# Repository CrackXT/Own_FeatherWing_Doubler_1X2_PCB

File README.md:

# Own_FeatherWing_Doubler_1X2_PCB

PCB files for two Adafruit Feather/FeatherWing on one PCB (side by side)

# Description

Two Feather/FeatherWing can be placed side by side on this board.

The Doubler 1X2, has a tripple duplicate breakout for each pin on a Feather, as well as a bunch of plain grid development holes. Also, the three sets of pins are cross connected and for GND(- or black) and 3.3V(+ or red), they give you a full strip of connected pads.

The board can be produced here (AISLER) with the files (.brd and .sch) or by any other PCB manufacturer. -> https://aisler.net/

# Serie

- .dev

# Layout

Top<br>

Bottom<br>

Routing/Dimensions(inch)<br>

Schematic<br>
Schematic as .pdf at the top of the page.

# License

The design and layout is based on open source publications from Adafruit and has been modified for side-by-side assembly.

# Thanks!

Great work and many thanks to Adafruit! https://www.adafruit.com/

# Version - Build

v1.0 - 21.01.2022

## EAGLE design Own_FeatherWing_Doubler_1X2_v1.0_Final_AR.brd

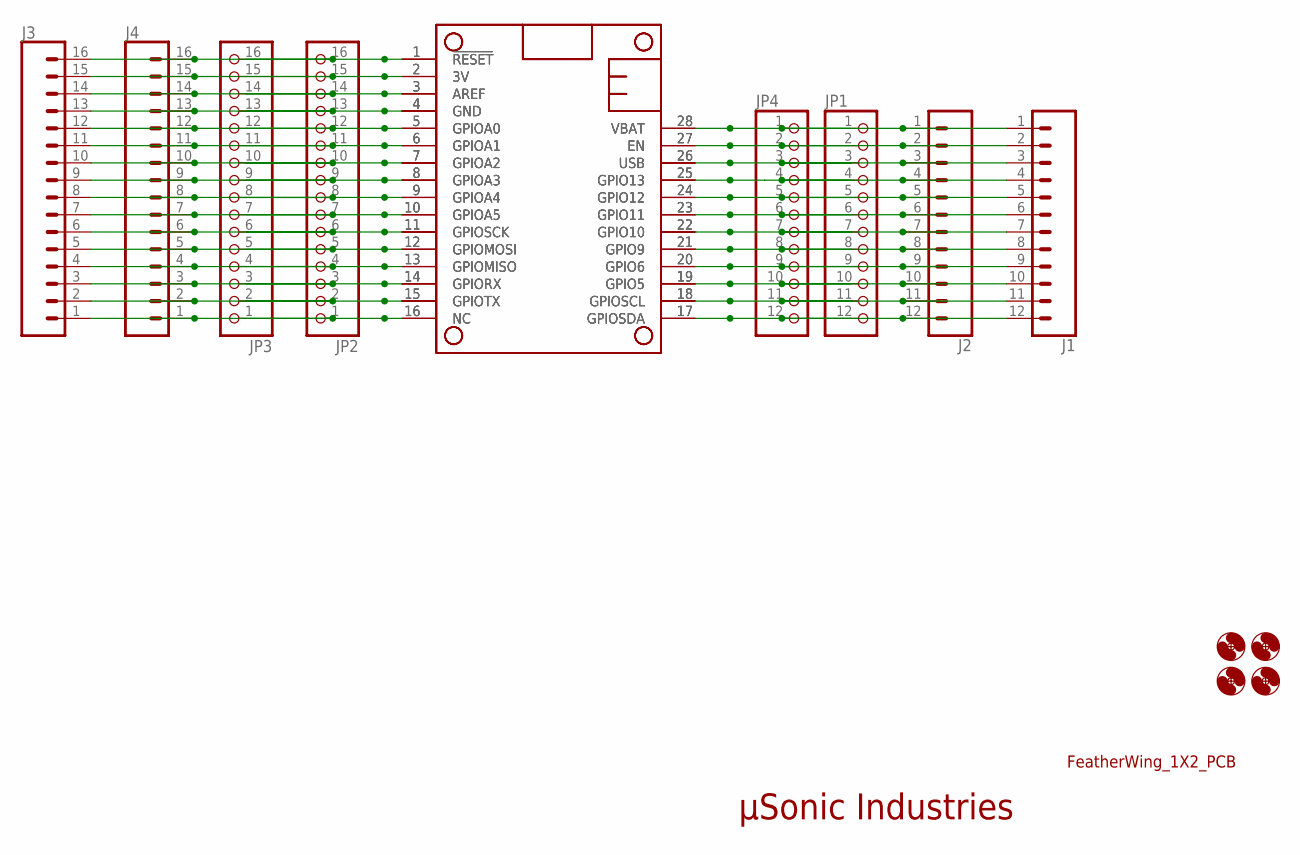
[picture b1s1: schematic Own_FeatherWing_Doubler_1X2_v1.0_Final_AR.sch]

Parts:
J1, J2: CONN_12NO_SILK; 1X12_NO_SILK
J3, J4: CONN_161X16_NO_SILK; 1X16_NO_SILK
JP1, JP4: HEADER-1X1276MIL; 1X12_ROUND_76MIL
JP2, JP3: HEADER-1X16_76MIL; 1X16_ROUND_76MIL
MS1, MS2: FEATHERWING_NODIM; FEATHERWING_DIM
U$2, U$3, U$4, U$5: MOUNTHOLEBIG; OWN_MOUNTHOLE_BIGAREA

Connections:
3V: J3.15, J4.15, JP2.15, JP3.15, MS1.2 (3V), MS2.2 (3V)
GND: J3.13, J4.13, JP2.13, JP3.13, MS1.4 (GND), MS2.4 (GND)
unnamed: J1.2, J2.2, JP1.2, JP4.2, MS1.27 (EN), MS2.27 (EN)
unnamed: J3.1, J4.1, JP2.1, JP3.1, MS1.16 (NC), MS2.16 (NC)
unnamed: J1.4, J2.4, JP1.4, JP4.4, MS1.25 (GPIO13), MS2.25 (GPIO13)
unnamed: J3.2, J4.2, JP2.2, JP3.2, MS1.15 (GPIOTX), MS2.15 (GPIOTX)
unnamed: J1.5, J2.5, JP1.5, JP4.5, MS1.24 (GPIO12), MS2.24 (GPIO12)
unnamed: J3.3, J4.3, JP2.3, JP3.3, MS1.14 (GPIORX), MS2.14 (GPIORX)
unnamed: J3.4, J4.4, JP2.4, JP3.4, MS1.13 (GPIOMISO), MS2.13 (GPIOMISO)
unnamed: J3.5, J4.5, JP2.5, JP3.5, MS1.12 (GPIOMOSI), MS2.12 (GPIOMOSI)
unnamed: J3.6, J4.6, JP2.6, JP3.6, MS1.11 (GPIOSCK), MS2.11 (GPIOSCK)
unnamed: J3.7, J4.7, JP2.7, JP3.7, MS1.10 (GPIOA5), MS2.10 (GPIOA5)
unnamed: J3.8, J4.8, JP2.8, JP3.8, MS1.9 (GPIOA4), MS2.9 (GPIOA4)
unnamed: J3.9, J4.9, JP2.9, JP3.9, MS1.8 (GPIOA3), MS2.8 (GPIOA3)
unnamed: J3.10, J4.10, JP2.10, JP3.10, MS1.7 (GPIOA2), MS2.7 (GPIOA2)
unnamed: J3.11, J4.11, JP2.11, JP3.11, MS1.6 (GPIOA1), MS2.6 (GPIOA1)
unnamed: J3.12, J4.12, JP2.12, JP3.12, MS1.5 (GPIOA0), MS2.5 (GPIOA0)
unnamed: J3.14, J4.14, JP2.14, JP3.14, MS1.3 (AREF), MS2.3 (AREF)
unnamed: J3.16, J4.16, JP2.16, JP3.16, MS1.1 (!RESET), MS2.1 (!RESET)
unnamed: J1.6, J2.6, JP1.6, JP4.6, MS1.23 (GPIO11), MS2.23 (GPIO11)
unnamed: J1.7, J2.7, JP1.7, JP4.7, MS1.22 (GPIO10), MS2.22 (GPIO10)
unnamed: J1.8, J2.8, JP1.8, JP4.8, MS1.21 (GPIO9), MS2.21 (GPIO9)
unnamed: J1.9, J2.9, JP1.9, JP4.9, MS1.20 (GPIO6), MS2.20 (GPIO6)
unnamed: J1.10, J2.10, JP1.10, JP4.10, MS1.19 (GPIO5), MS2.19 (GPIO5)
unnamed: J1.11, J2.11, JP1.11, JP4.11, MS1.18 (GPIOSCL), MS2.18 (GPIOSCL)
unnamed: J1.12, J2.12, JP1.12, JP4.12, MS1.17 (GPIOSDA), MS2.17 (GPIOSDA)
USB: J1.3, J2.3, JP1.3, JP4.3, MS1.26 (USB), MS2.26 (USB)
VBAT: J1.1, J2.1, JP1.1, JP4.1, MS1.28 (VBAT), MS2.28 (VBAT)

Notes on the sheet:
FeatherWing_1X2_PCB
µSonic Industries

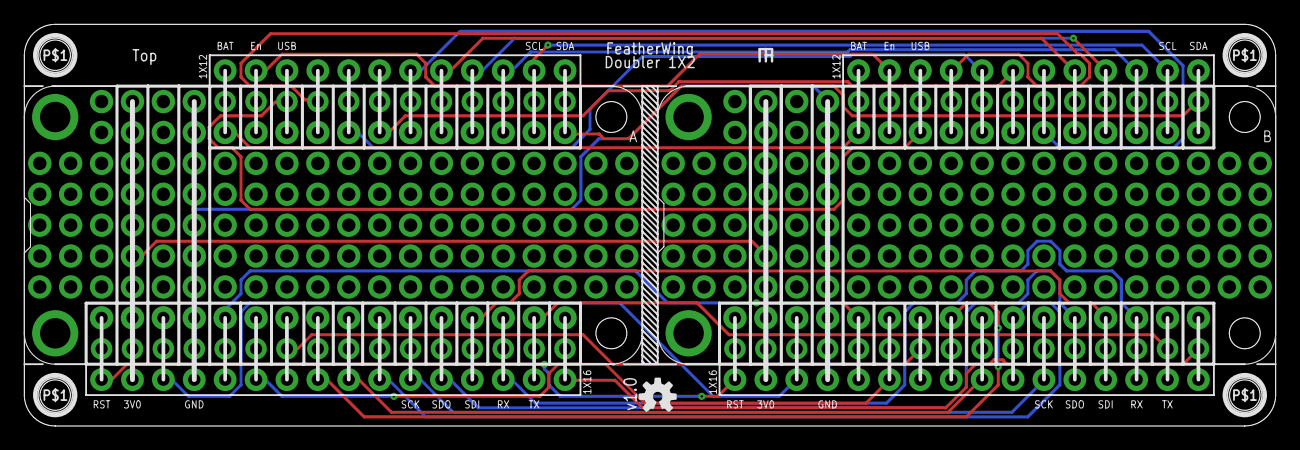
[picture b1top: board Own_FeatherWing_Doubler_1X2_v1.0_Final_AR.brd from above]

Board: 2 copper layers, 102.9 x 33.0 mm, 15 parts (0 on the bottom side), 28 nets.

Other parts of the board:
U$6: OSHW-LOGO-S

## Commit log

2022-01-21 Create changelog
2022-01-21 Update changelog
2022-01-21 Create BOM
2022-01-21 Update BOM
2022-01-21 Rename BOM to BOM.md

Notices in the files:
parts and their libraries:
SparkFun-Aesthetics: Licensing: Creative Commons ShareAlike 4.0 International - https://creativecommons.org/licenses/by-sa/4.0
